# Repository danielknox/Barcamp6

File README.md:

# Barcamp6
Puzzle and Badges for Barcamp 6

Barcamp 6's theme was loosely based around the film The Fifth Element. Throughout the day a puzzle game played out for the 50+ attendees. In this repo are the files that made up the game. 

The badges, given to each attendee, are used to provide a clue to each tribe to locate their artefact and are used as part of the end sequence animation. They also fade their lights in/out approximately every 8 seconds (which looks quite cool when people are speaking/sitting in groups). 

The pcbs and puzzles took about two months to develop and produce. 

Special thanks to: 
Keith Greenhow (helped develop a number of the puzzles -- like the fourtime pad
Martin Falkner (for helping to assemble 40+ pcbs!)

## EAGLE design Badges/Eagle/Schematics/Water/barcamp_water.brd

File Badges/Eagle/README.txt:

Gerbers should contain the ready to go files, schematics contains the Eagle board files.

Fabrication:
I used SEEEDSTUDIO for board fabrication.

For production, Barcamp stencil was used with bi-directional engraving on laser cutter using OHP asertate. Laser outline was used to create a simple nested jig (0.1mm offset).
Use ducktape to secure acertate to jig and paste away!

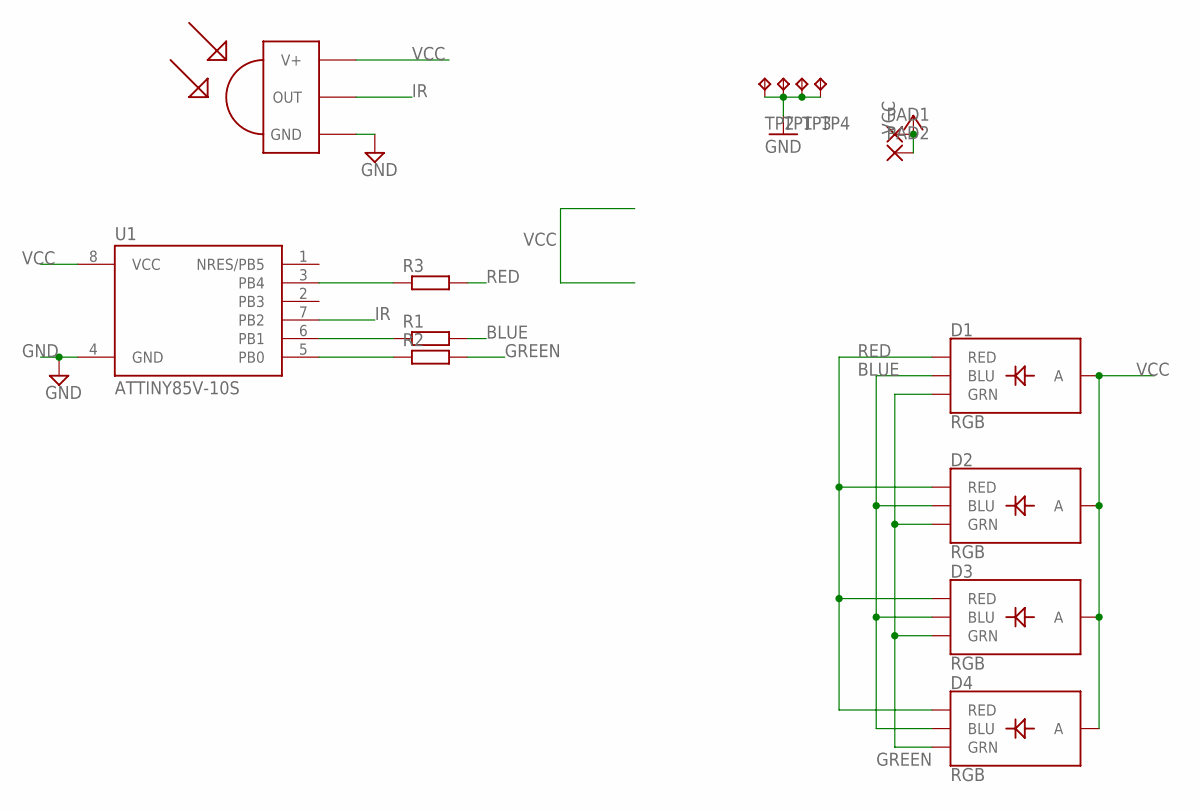
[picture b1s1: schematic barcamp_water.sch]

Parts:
D1, D2, D3, D4: RGB; P-LCC-4-3
PAD1, PAD2: 3,17/1,3
R1, R2: 12ohm; R0603
R3: R-EU_R0603; R0603
TP1, TP2, TP3, TP4: TPTP20SQ; TP20SQ
U1: ATTINY85V-10S; SOIC8_EIAJ_208MIL
U$1: TSOP4838; TSOP18XX

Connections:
BLUE: D1.3 (BLU), D2.3 (BLU), D3.3 (BLU), D4.3 (BLU), R1.2
GND: TP1.TP, TP2.TP, TP3.TP, TP4.TP, U1.4 (GND), U$1.GND
GREEN: D1.2 (GRN), D2.2 (GRN), D3.2 (GRN), D4.2 (GRN), R2.2
IR: U1.7 (PB2), U$1.OUT
unnamed: R1.1, U1.6 (PB1)
unnamed: R2.1, U1.5 (PB0)
unnamed: R3.1, U1.3 (PB4)
RED: D1.1 (RED), D2.1 (RED), D3.1 (RED), D4.1 (RED), R3.2
VCC: D1.4 (A), D2.4 (A), D3.4 (A), D4.4 (A), PAD1.1, PAD2.1, U1.8 (VCC), U$1.VCC (V+)

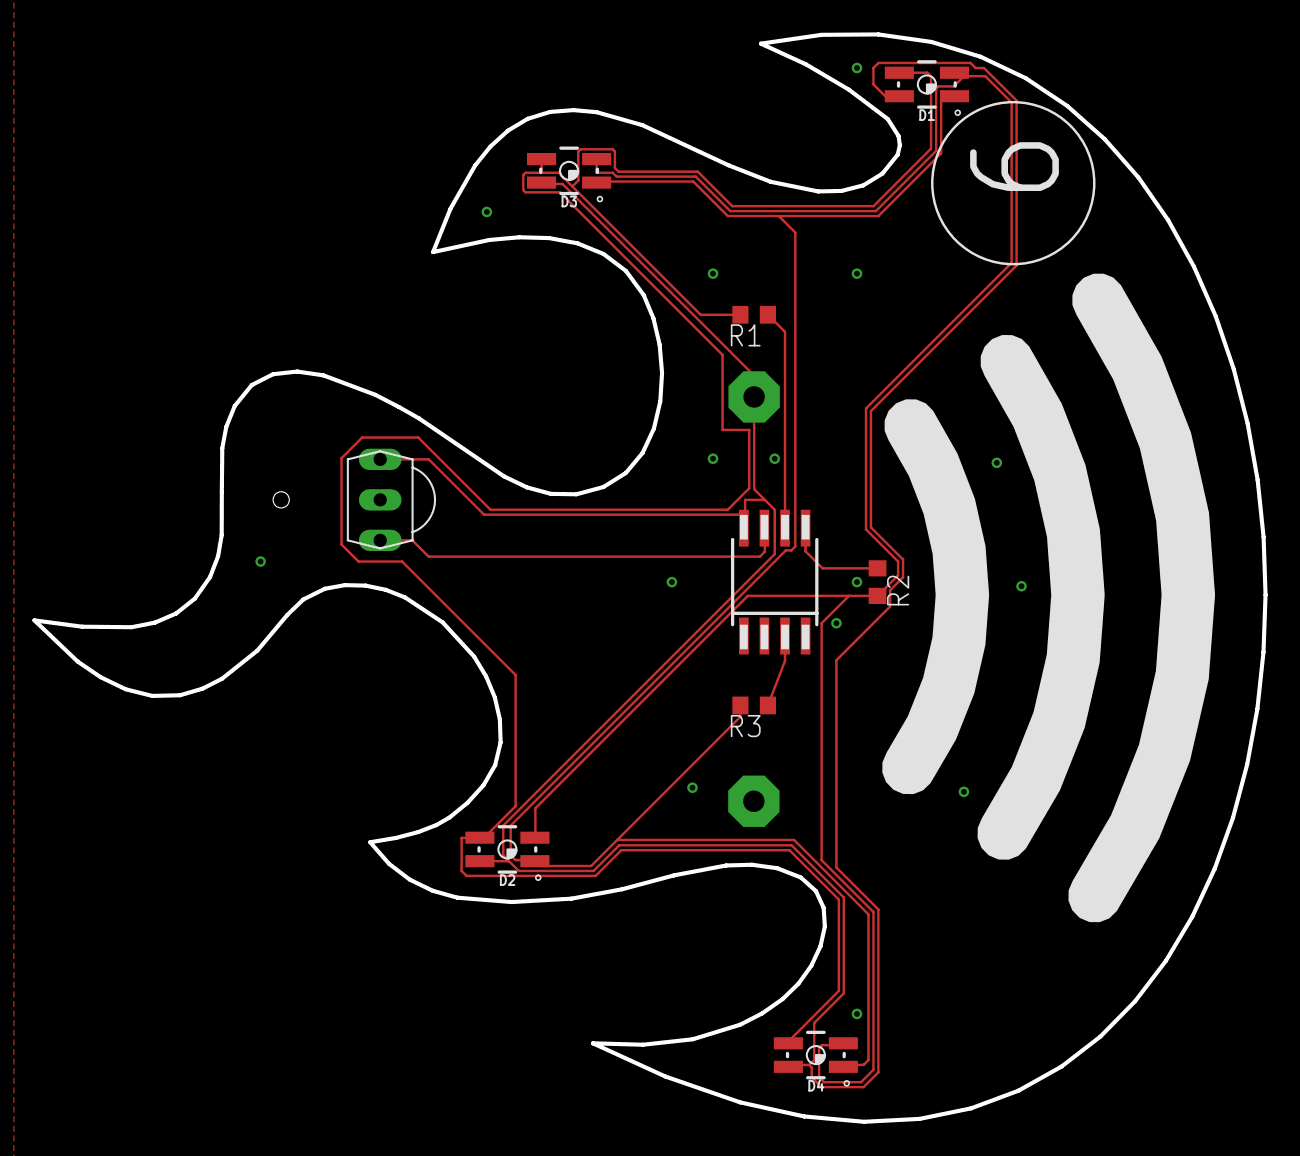
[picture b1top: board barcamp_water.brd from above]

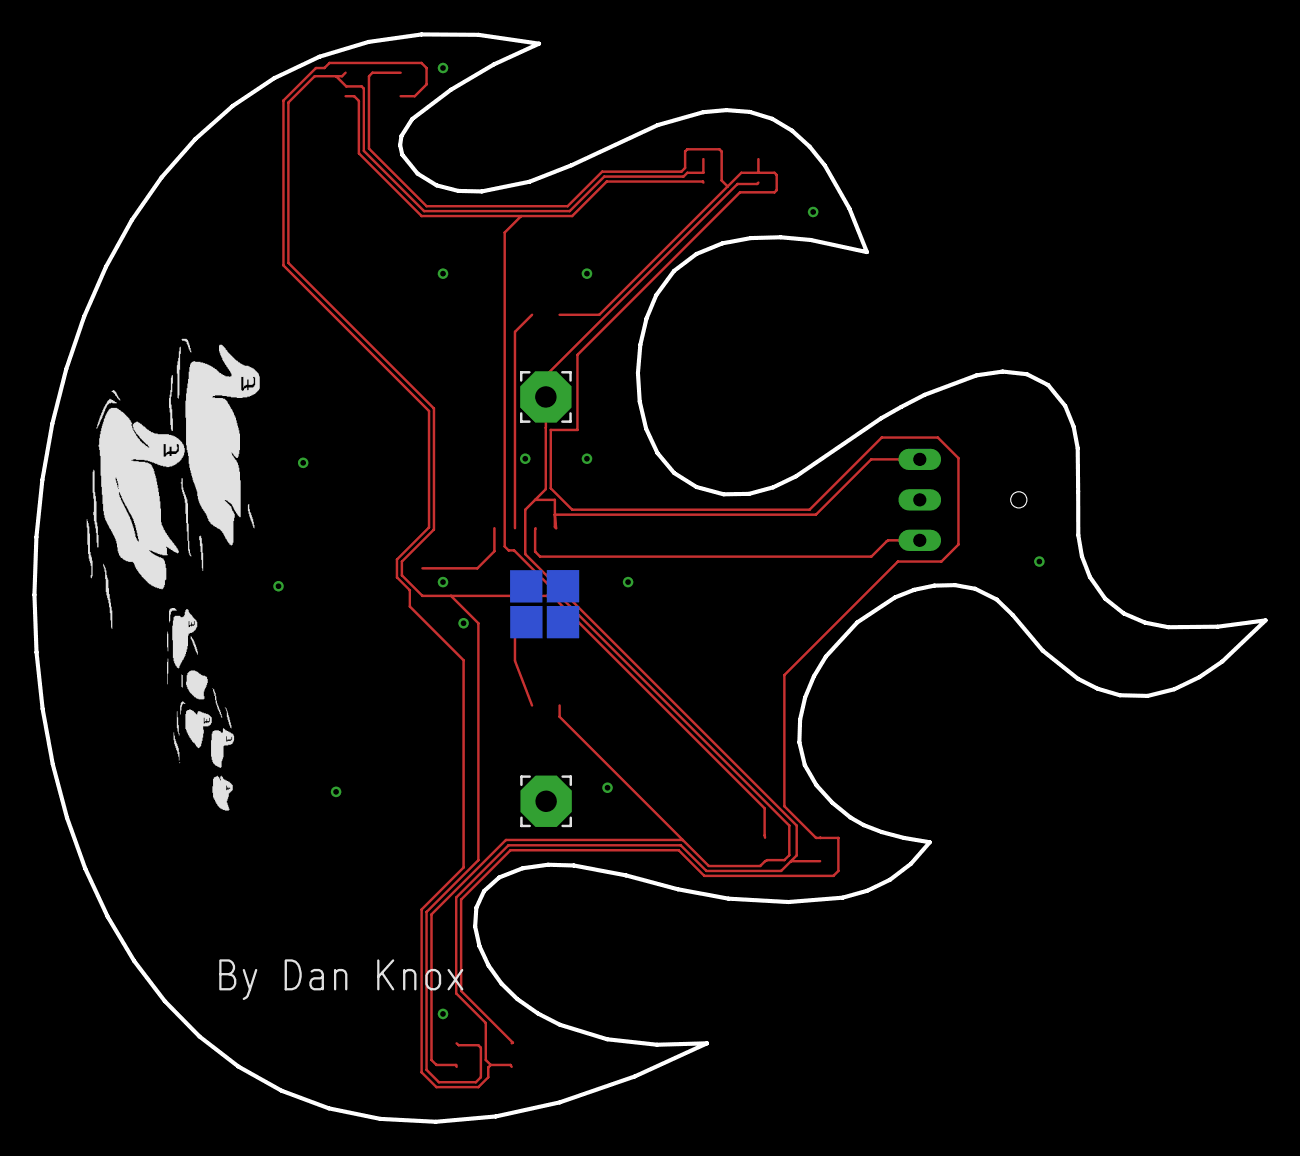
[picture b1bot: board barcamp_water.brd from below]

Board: 2 copper layers, 76.0 x 67.2 mm, 15 parts (6 on the bottom side), 9 nets.

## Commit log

2019-06-10 code files
2019-06-10 images

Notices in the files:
parts and their libraries:
SparkFun-LED: Licensing: Creative Commons ShareAlike 4.0 International - https://creativecommons.org/licenses/by-sa/4.0
